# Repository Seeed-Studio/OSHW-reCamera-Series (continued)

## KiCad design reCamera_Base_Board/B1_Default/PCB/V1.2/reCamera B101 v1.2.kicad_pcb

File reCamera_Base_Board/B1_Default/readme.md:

## B1_Default
🎈🎈🎈🎈🎈🎈🎈🎈🎈

**The project contains the 3D housing and circuit design files of the cover board.**

You can use this project to make your own PCB, and the design drawing can also be used as a basic reference for your design.

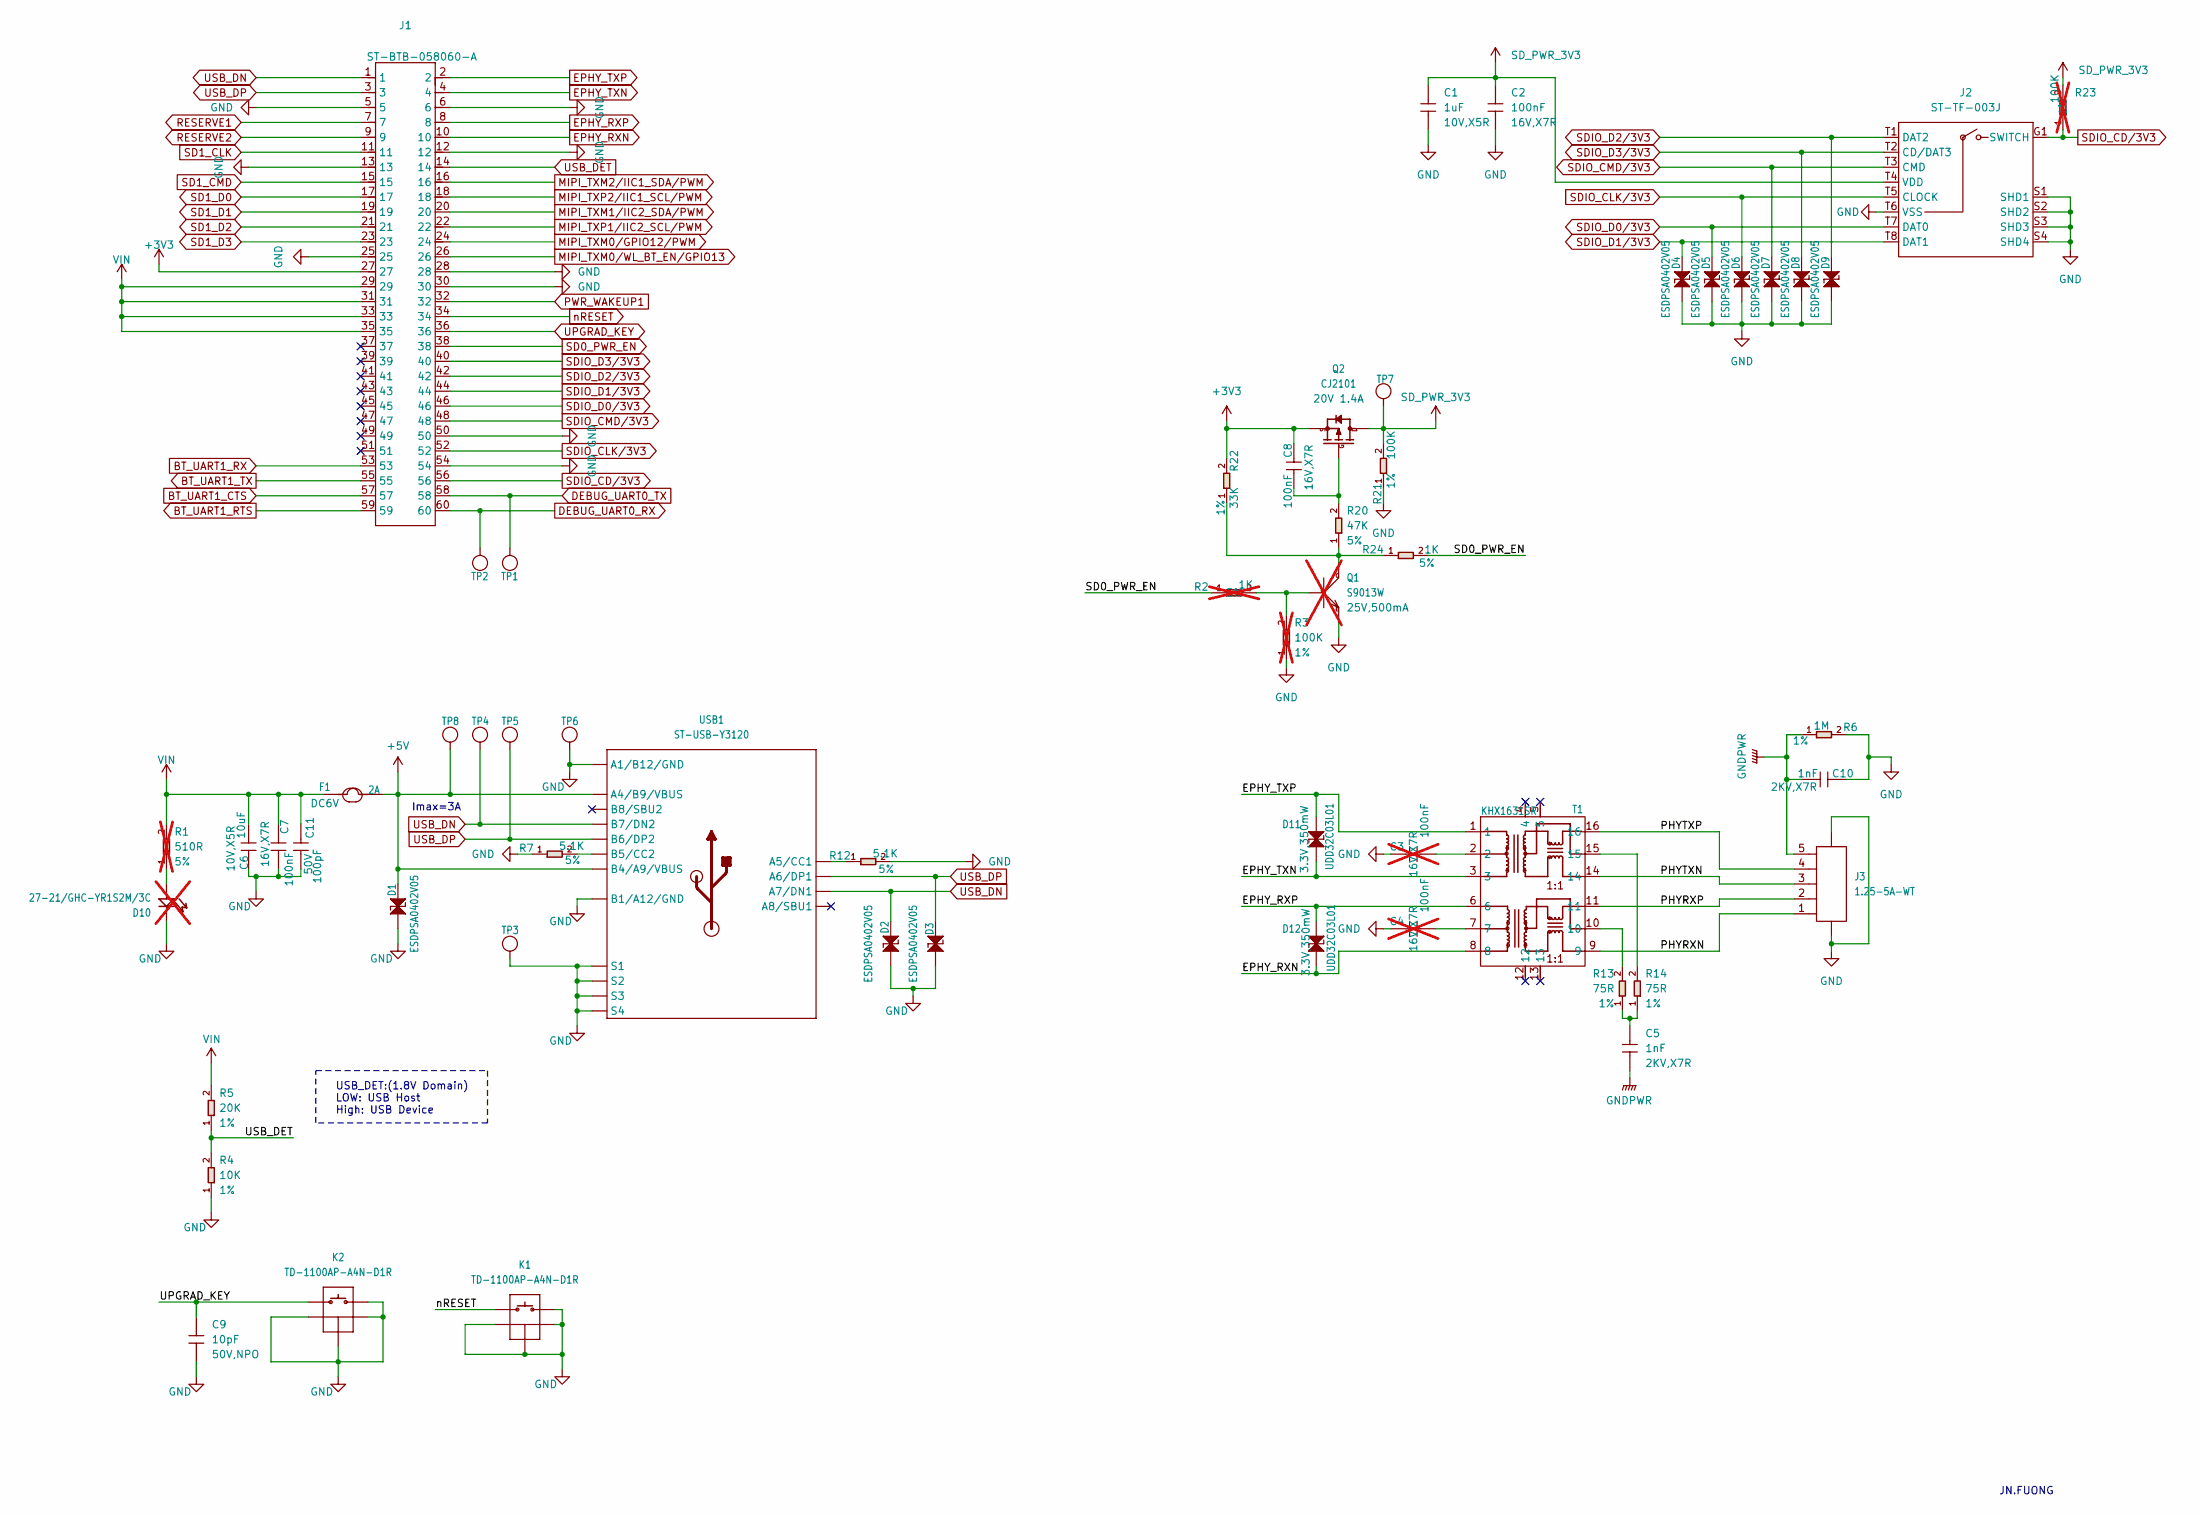
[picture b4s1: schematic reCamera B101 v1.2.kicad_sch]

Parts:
C1: 1uF; C0402; Voltage Rating 10V,X5R; MPN CC0402KRX5R6BB105
C2, C7, C8: 100nF; C0402; Voltage Rating 16V,X7R; MPN CC0402KRX7R7BB104
C3, C4: 100nF; C0402; Voltage Rating 16V,X7R; MPN CC0402KRX7R7BB104; not fitted
C5, C10: 1nF; C1206; Voltage Rating 2KV,X7R; MPN CC1206KKX7RDBB102
C6: 10uF; C0603; Voltage Rating 10V,X5R; MPN CC0603KRX5R6BB106
C9: 10pF; C0402; Voltage Rating 50V,NPO; MPN CC0402JRNPO9BN100
C11: 100pF; C0402; Voltage Rating 50V; MPN CC0402JRNPO9BN101
D1, D2, D3, D4, D5, D6, D7, D8, D9: ESDPSA0402V05; ESD-0402; MPN ESDPSA0402V05
D10: 27-21/GHC-YR1S2M/3C; LED2-0.6X1.7MM; MPN 27-21/GHC-YR1S2M/3C; not fitted
D11, D12: UDD32C03L01; SOD-323; Rating 3.3V,350mW; MPN UDD32C03L01
F1: 2A; F1210; Rating DC6V; MPN SMD1210R200SF
J1: ST-BTB-058060-A; BTB60-Male-Female-0.5-17.7x4.4mm; MPN ST-BTB-058060-A
J2: ST-TF-003J; MICRO-SD-CARD-9P; MPN ST-TF-003J
J3: 1.25-5A-WT; JST5_2P_1d25_7_9x4_3x3_4mm; MPN 1.25-5A-WT
K1, K2: TD-1100AP-A4N-D1R; SW5-SMD-4.56X2.3X1.9MM; MPN TD-1100AP-A4N-D1R
Q1: S9013W; SOT-323; Rating 25V,500mA; MPN S9013W; not fitted
Q2: CJ2101; SOT-323; Rating 20V 1.4A; MPN CJ2101
R1: 510R; R0402; Power Rating 5%; MPN RC0402JR-07510RL; not fitted
R2: 1K; R0402; Power Rating 5%; MPN RC0402JR-071KL; not fitted
R3, R23: 100K; R0402; Power Rating 1%; MPN RC0402FR-07100KL; not fitted
R4: 10K; R0402; Power Rating 1%; MPN RC0402FR-0710KL
R5: 20K; R0402; Power Rating 1%; MPN RC0402FR-0720KL
R6: 1M; R1206; Power Rating 1%; MPN RC1206FR-071ML
R7, R12: 5.1K; R0402; Power Rating 5%; MPN RC0402JR-075K1L
R13, R14: 75R; R0603; Power Rating 1%; MPN RC0603FR-0775RL
R20: 47K; R0402; Power Rating 5%; MPN RC0402JR-0747KL
R21: 100K; R0402; Power Rating 1%; MPN RC0402FR-07100KL
R22: 33K; R0402; Power Rating 1%; MPN RC0402FR-0733KL
R24: 1K; R0402; Power Rating 5%; MPN RC0402JR-071KL
T1: KHX1631SR; TRF_16p_1d27_12d7x7d15x5d1mm; MPN KHX1631SR
TP1, TP2, TP3: Test Point; TP-80X40MIL; Part Type Test Point
TP4, TP5, TP6, TP7, TP8: Test Point; TP-D35MIL; Part Type Test Point
USB1: ST-USB-Y3120; USB2.0-TYPE-C-SMD-12X7.35X3.3MM; MPN ST-USB-Y3120

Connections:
+3V3: C8.1, J1.27, Q2.2 (S), R22.2
+5V: D1.1, F1.2, TP8.1 (T), USB1.A4_B9 (A4/B9/VBUS), USB1.B4_A9 (B4/A9/VBUS)
/PHYRXN: J3.1, T1.9
/PHYRXP: J3.2, T1.11
/PHYTXN: J3.3, T1.14
/PHYTXP: J3.4, T1.16
BT_UART1_CTS: J1.57
BT_UART1_RTS: J1.59
BT_UART1_RX: J1.53
BT_UART1_TX: J1.55
DEBUG_UART0_RX: J1.60, TP2.1 (T)
DEBUG_UART0_TX: J1.58, TP1.1 (T)
EPHY_RXN: D12.1, J1.10, T1.8
EPHY_RXP: D12.2, J1.8, T1.6
EPHY_TXN: D11.1, J1.4, T1.3
EPHY_TXP: D11.2, J1.2, T1.1
GND: C1.2, C2.2, C3.1, C4.1, C6.2, C7.2, C9.2, C10.1, C11.2, D1.2, D2.2, D3.2, D4.2, D5.2, D6.2, D7.2, D8.2, D9.2, D10.2 (-), J1.5, J1.6, J1.12, J1.13, J1.25, J1.28, J1.30, J1.50, J1.54, J2.S1 (SHD1), J2.S2 (SHD2), J2.S3 (SHD3), J2.S4 (SHD4), J2.T6 (VSS), J3.6, J3.7, K1.2, K1.S1, K1.S2, K1.S3, K2.2, K2.S1, K2.S2, K2.S3, Q1.2 (E), R3.1, R4.1, R6.2, R7.1, R12.2, R21.1, TP3.1 (T), TP6.1 (T), USB1.A1_B12 (A1/B12/GND), USB1.B1_A12 (B1/A12/GND), USB1.S1, USB1.S2, USB1.S3, USB1.S4
GNDPWR: C5.2, C10.2, J3.5, R6.1
MIPI_TXM0/GPIO12/PWM: J1.24
MIPI_TXM0/WL_BT_EN/GPIO13: J1.26
MIPI_TXM1/IIC2_SDA/PWM: J1.20
MIPI_TXM2/IIC1_SDA/PWM: J1.16
MIPI_TXP1/IIC2_SCL/PWM: J1.22
MIPI_TXP2/IIC1_SCL/PWM: J1.18
unnamed: C3.2, T1.2
unnamed: C4.2, T1.7
unnamed: C5.1, R13.1, R14.1
unnamed: D10.1 (+), R1.1
unnamed: Q1.1 (B), R2.2, R3.2
unnamed: Q1.3 (C), R20.1, R22.1, R24.1
unnamed: C8.2, Q2.1 (G), R20.2
unnamed: R13.2, T1.10
unnamed: R14.2, T1.15
unnamed: R12.1, USB1.A5 (A5/CC1)
unnamed: R7.2, USB1.B5 (B5/CC2)
PWR_WAKEUP1: J1.32
RESERVE1: J1.7
RESERVE2: J1.9
SD0_PWR_EN: J1.38, R2.1, R24.2
SD1_CLK: J1.11
SD1_CMD: J1.15
SD1_D0: J1.17
SD1_D1: J1.19
SD1_D2: J1.21
SD1_D3: J1.23
SDIO_CD/3V3: J1.56, J2.G1 (SWITCH), R23.1
SDIO_CLK/3V3: D6.1, J1.52, J2.T5 (CLOCK)
SDIO_CMD/3V3: D7.1, J1.48, J2.T3 (CMD)
SDIO_D0/3V3: D5.1, J1.46, J2.T7 (DAT0)
SDIO_D1/3V3: D4.1, J1.44, J2.T8 (DAT1)
SDIO_D2/3V3: D9.1, J1.42, J2.T1 (DAT2)
SDIO_D3/3V3: D8.1, J1.40, J2.T2 (CD/DAT3)
SD_PWR_3V3: C1.1, C2.1, J2.T4 (VDD), Q2.3 (D), R21.2, R23.2, TP7.1 (T)
UPGRAD_KEY: C9.1, J1.36, K2.1
USB_DET: J1.14, R4.2, R5.1
USB_DN: D2.1, J1.1, TP4.1 (T), USB1.A7 (A7/DN1), USB1.B7 (B7/DN2)
USB_DP: D3.1, J1.3, TP5.1 (T), USB1.A6 (A6/DP1), USB1.B6 (B6/DP2)
VIN: C6.1, C7.1, C11.1, F1.1, J1.29, J1.31, J1.33, J1.35, R1.2, R5.2
nRESET: J1.34, K1.1

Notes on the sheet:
JN.FUONG
USB_DET:(1.8V Domain) LOW: USB Host High: USB Device
Imax=3A

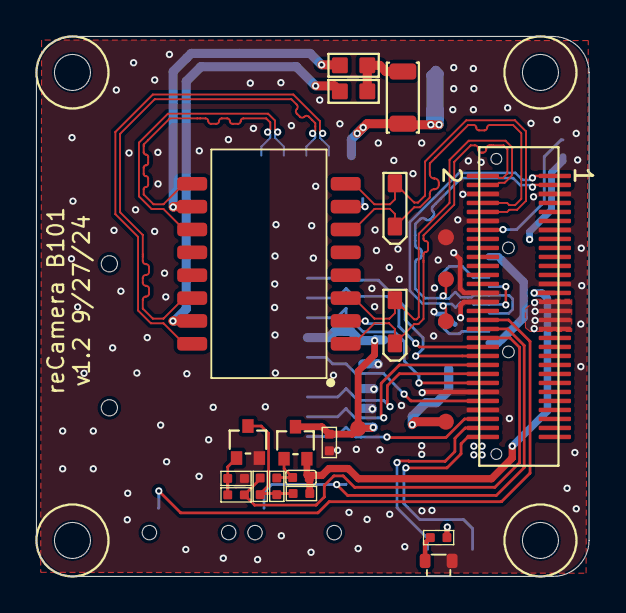
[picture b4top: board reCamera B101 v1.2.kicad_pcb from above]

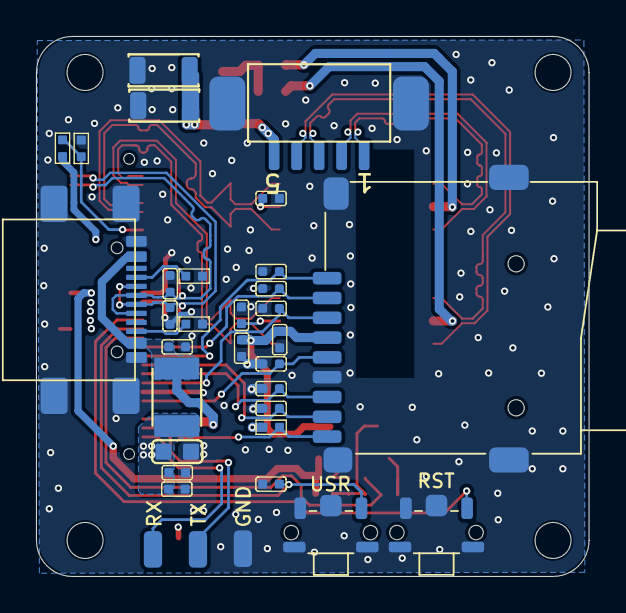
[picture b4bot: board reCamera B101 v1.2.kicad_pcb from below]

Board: 4 copper layers, 30.7 x 30.0 mm, 56 parts (33 on the bottom side), 40 nets.

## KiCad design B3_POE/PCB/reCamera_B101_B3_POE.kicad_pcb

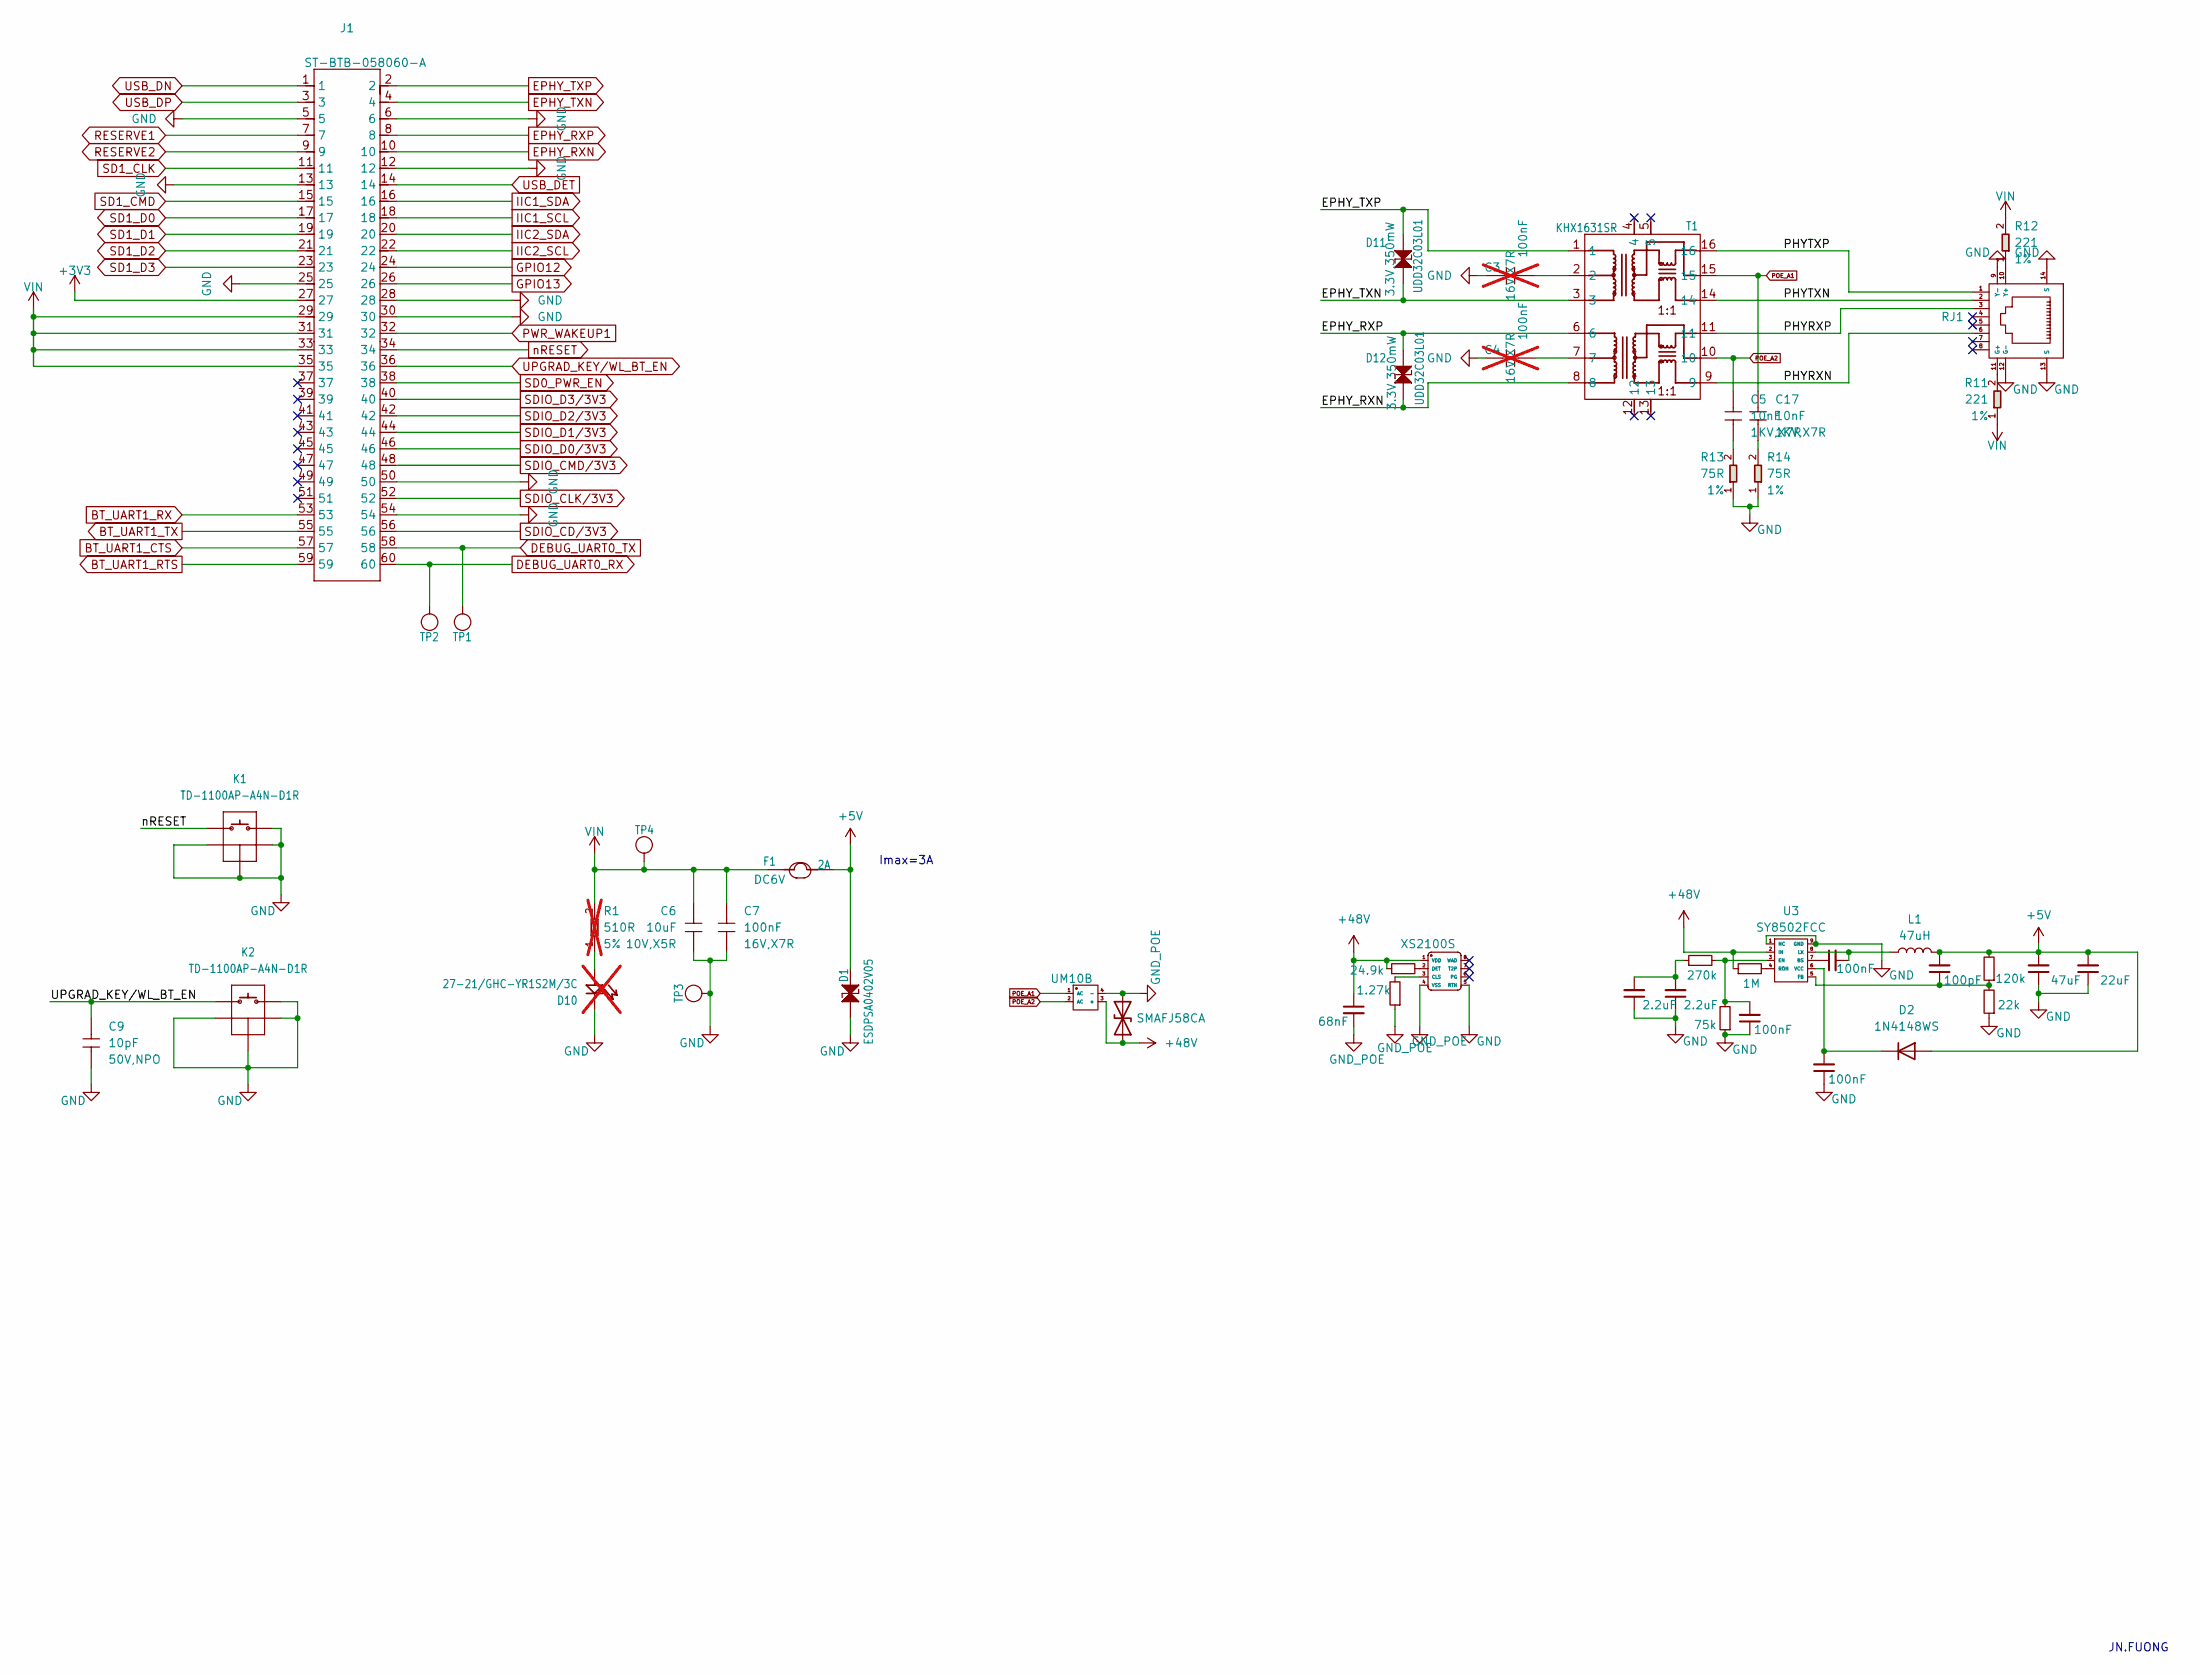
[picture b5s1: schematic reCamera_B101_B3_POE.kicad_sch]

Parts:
C1: 68nF; C_0402_1005Metric
C2, C10: 2.2uF; C_0402_1005Metric
C3, C4: 100nF; C0402; Voltage Rating 16V,X7R; MPN CC0402KRX7R7BB104; not fitted
C5, C17: 10nF; C0402; Voltage Rating 1KV,X7R; MPN CC1206KKX7RCBB102
C6: 10uF; C0402; Voltage Rating 10V,X5R; MPN CC0603KRX5R6BB106
C7: 100nF; C0402; Voltage Rating 16V,X7R; MPN CC0402KRX7R7BB104
C9: 10pF; C0402; Voltage Rating 50V,NPO; MPN CC0402JRNPO9BN100
C11, C12, C13: 100nF; C_0402_1005Metric
C14: 100pF; C_0402_1005Metric
C15: 47uF; C_0402_1005Metric
C16: 22uF; C_0402_1005Metric
D1: ESDPSA0402V05; ESD-0402; MPN ESDPSA0402V05
D2: 1N4148WS; D_SOD-323
D10: 27-21/GHC-YR1S2M/3C; LED2-0.6X1.7MM; MPN 27-21/GHC-YR1S2M/3C; not fitted
D11, D12: UDD32C03L01; SOD-323; Rating 3.3V,350mW; MPN UDD32C03L01
D13: SMAFJ58CA; SMAF_L3.5-W2.6-LS4.7-BI
F1: 2A; F1210; Rating DC6V; MPN SMD1210R200SF
J1: ST-BTB-058060-A; BTB60-Male-Female-0.5-17.7x4.4mm; MPN ST-BTB-058060-A
K1, K2: TD-1100AP-A4N-D1R; SW5-SMD-4.56X2.3X1.9MM; MPN TD-1100AP-A4N-D1R
L1: 47uH; L_7.3x7.3_H3.5
R1: 510R; R0402; Power Rating 5%; MPN RC0402JR-07510RL; not fitted
R4: 1.27k; R_0402_1005Metric
R5: 24.9k; R_0402_1005Metric
R6: 270k; R_0402_1005Metric
R7: 75k; R_0402_1005Metric
R8: 1M; R_0402_1005Metric
R9: 120k; R_0402_1005Metric
R10: 22k; R_0402_1005Metric
R11, R12: 221; C0402; Power Rating 1%; MPN RC0603FR-0775RL
R13, R14: 75R; C0402; Power Rating 1%; MPN RC0603FR-0775RL
RJ1: R-RJ45S08P-C000
T1: KHX1631SR; TRF_16p_1d27_12d7x7d15x5d1mm; MPN KHX1631SR
TP1, TP2, TP3, TP4: Test Point; TP; Part Type Test Point
U1: UM10B; UMB-4_L3.8-W3.6-P2.50-LS4.9-BL
U2: XS2100S; SOP-8_L4.9-W3.9-P1.27-LS6.0-BL
U3: SY8502FCC; SOIC-8_L4.9-W3.9-P1.27-LS6.0-BL-EP

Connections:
+3V3: J1.27
+5V: C14.2, C15.2, C16.2, D1.1, D2.2 (A), F1.2, L1.2, R9.2
+48V: C1.1, D13.1 (A1), R5.1, R8.1, U1.3 (+), U2.1 (VDD), U3.2 (IN)
/PHYRXN: RJ1.6, T1.9
/PHYRXP: RJ1.3, T1.11
/PHYTXN: RJ1.2, T1.14
/PHYTXP: RJ1.1, T1.16
BT_UART1_CTS: J1.57
BT_UART1_RTS: J1.59
BT_UART1_RX: J1.53
BT_UART1_TX: J1.55
DEBUG_UART0_RX: J1.60, TP2.1 (T)
DEBUG_UART0_TX: J1.58, TP1.1 (T)
EPHY_RXN: D12.1, J1.10, T1.8
EPHY_RXP: D12.2, J1.8, T1.6
EPHY_TXN: D11.1, J1.4, T1.3
EPHY_TXP: D11.2, J1.2, T1.1
GND: C2.1, C3.1, C4.1, C6.2, C7.2, C9.2, C10.1, C11.1, C12.1, C15.1, C16.1, D1.2, D10.2 (-), J1.5, J1.6, J1.12, J1.13, J1.25, J1.28, J1.30, J1.50, J1.54, K1.2, K1.S1, K1.S2, K1.S3, K2.2, K2.S1, K2.S2, K2.S3, R7.1, R10.1, R13.1, R14.1, RJ1.9 (Y-), RJ1.12 (G-), RJ1.13 (S), RJ1.14 (S), TP3.1 (T), U2.5 (RTN), U3.1 (NC), U3.9 (GND)
GND_POE: C1.2, D13.2 (A2), R4.1, U1.4 (-), U2.4 (VSS)
GPIO12: J1.24
GPIO13: J1.26
IIC1_SCL: J1.18
IIC1_SDA: J1.16
IIC2_SCL: J1.22
IIC2_SDA: J1.20
unnamed: C3.2, T1.2
unnamed: C4.2, T1.7
unnamed: C5.2, R13.2
unnamed: C2.2, C10.2, R6.1
unnamed: C17.2, R14.2
unnamed: C12.2, D2.1 (K), U3.6 (VCC)
unnamed: D10.1 (+), R1.1
unnamed: R11.2, RJ1.11 (G+)
unnamed: R12.1, RJ1.10 (Y+)
unnamed: R4.2, U2.3 (CLS)
unnamed: R5.2, U2.2 (DET)
unnamed: C13.1, U3.7 (BS)
unnamed: C11.2, R6.2, R7.2, U3.3 (EN)
unnamed: C14.1, R9.1, R10.2, U3.5 (FB)
unnamed: C13.2, L1.1, U3.8 (LX)
unnamed: R8.2, U3.4 (RON)
POE_A1: C17.1, T1.15, U1.1 (AC)
POE_A2: C5.1, T1.10, U1.2 (AC)
PWR_WAKEUP1: J1.32
RESERVE1: J1.7
RESERVE2: J1.9
SD0_PWR_EN: J1.38
SD1_CLK: J1.11
SD1_CMD: J1.15
SD1_D0: J1.17
SD1_D1: J1.19
SD1_D2: J1.21
SD1_D3: J1.23
SDIO_CD/3V3: J1.56
SDIO_CLK/3V3: J1.52
SDIO_CMD/3V3: J1.48
SDIO_D0/3V3: J1.46
SDIO_D1/3V3: J1.44
SDIO_D2/3V3: J1.42
SDIO_D3/3V3: J1.40
UPGRAD_KEY/WL_BT_EN: C9.1, J1.36, K2.1
USB_DET: J1.14
USB_DN: J1.1
USB_DP: J1.3
VIN: C6.1, C7.1, F1.1, J1.29, J1.31, J1.33, J1.35, R1.2, R11.1, R12.2, TP4.1 (T)
nRESET: J1.34, K1.1

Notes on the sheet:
JN.FUONG
Imax=3A

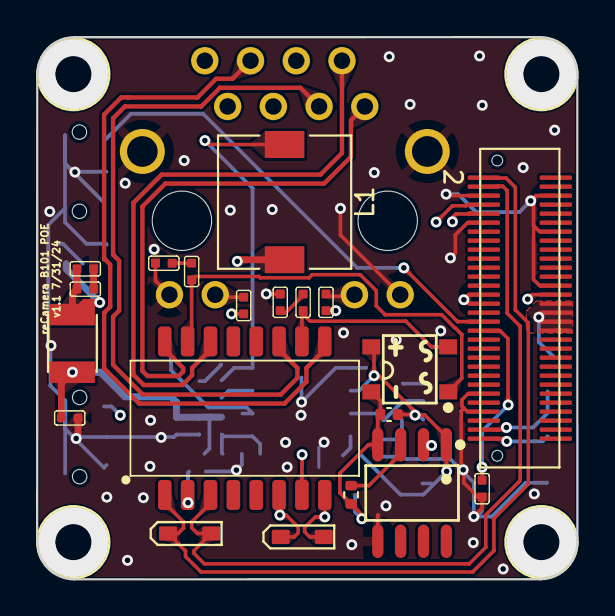
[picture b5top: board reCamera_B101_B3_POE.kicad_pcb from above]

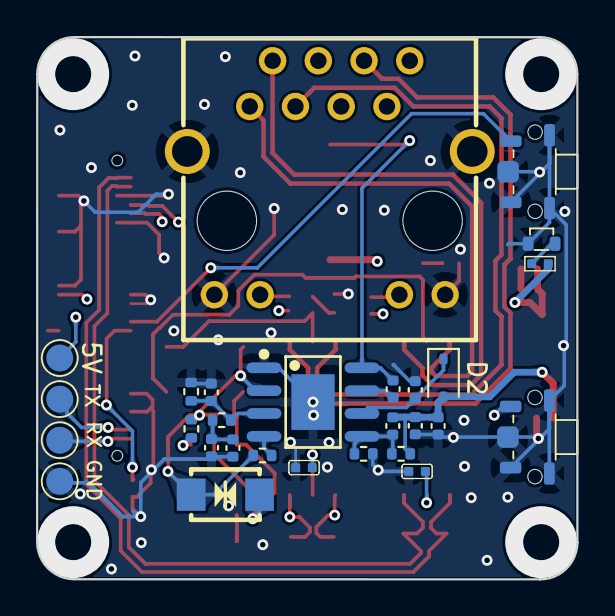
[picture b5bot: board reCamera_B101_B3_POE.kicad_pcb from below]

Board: 4 copper layers, 30.0 x 30.1 mm, 48 parts (28 on the bottom side), 35 nets.

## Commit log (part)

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2024-08-01 docs: project structure init
2024-08-06 [doc] add standard boards readme
2024-08-06 [fix] use raw html for image
2024-08-06 [fix] restore readme.md
2024-08-07 [fix] revise the readme.md
2024-08-07 [fix] Add reCamera-Gimbal-1.png
2024-08-07 [fix] S1_OV5647/s101-readme.md: fix typo
2024-08-07 [fix] change the camera name to OV5647
2024-08-07 [fix] Update S1_OV5647/s101-readme.md
2024-08-07 [fix] add Model for OV5647 camera
2024-08-09 [fix]: reCamera is not ReCamera
2024-08-13 [fix]
2024-08-15 [doc] update software projects
2024-08-15 Rename 20b716f188346082ae41970eb1b7215.png to B1_Default_Bottom.png
2024-08-15 Rename 233ed49bf09d4f877fda6c783545a1c.png to B1_Default_Upper.png
2024-08-15 Rename a1820e9c1d215a653db6a6fbe115e7e.png to B1_Default_sch.png
2024-08-15 Rename efaac50a4a5e071a0dab4a029c1c640.png to B1_POE_sch.png
2024-08-15 Rename B1_Default/recamera_B1_.stp to B1_Default/Model/recamera_B1_Default.stp
2024-08-15 Rename B1_Default/reCamera B101 v0.1.kicad_pro to B1_Default/PCB/reCamera B101 v0.1.kicad_pro
2024-08-15 Rename B2_POE/reCamera_B101_RJ45.kicad_pro to B2_POE/PCB/reCamera_B101_RJ45.kicad_pro
2024-08-15 chore: Update core board features and version info
2024-08-15 File structure changed
2024-08-15 Fix image paths in readme.md
2024-08-15 picture change
2024-08-15 Update core board features and version info
2024-08-15 Upload the New Board
2024-08-16 PIC changed
2024-08-16 Changed B3 and B4
2024-08-16 [fix] add readme.md and statics
2024-08-16 [fix]add images
2024-08-16 Add S2_IMX335 and S3_SC130GS readme files
2024-08-19 chore: Update reCamera Web frontend link
2024-08-19 POE Changed
2024-08-20 chore: Fix typo in readme.md
2024-08-20 Create LICENSE
2024-08-21 chore: Update reCamera Gimbal image in readme.md
2024-08-22 [fix]add Sensor list
2024-08-23 Rename 企业微信截图_17243809714874.png to B3_POE_sch.png
2024-08-23 Rename reCamera_B101_RJ45.kicad_pro to reCamera_B101_POE.kicad_pro
2024-08-24 Add discord link
2024-08-24 chore: Add Discord group invitation link to readme.md
2024-09-09 PoE Modified
2024-09-11 B101 V1.0 & V1.1
2024-09-11 reCamera_Pocket
2024-09-11 reCamera_pocket update
2024-09-11 pocket
2024-09-18 Rename 427b60a50cdec68b545c81bb3820fad.png to B3_POE_sch.png
2024-10-08 Add sync_issues GitHub Action for workflows
2024-10-23 [fix]add C1 PCB files
2024-11-01 Update C1, B1, S1
2024-11-01 Change C1 Board file path
2024-11-01 update files
2024-11-01 Update readme.md with social media sharing buttons and badges
2024-11-14 [fix]changed readme
2024-11-29 update B1 S1 C1 board image
2024-12-03 [fix]changed images
2024-12-10 [fix]add Gimbal files
2024-12-10 [fix]changed reCamera_Gimbal
2024-12-10 [fix]change readme.md
2024-12-11 [fix]change recamera Gimbal files
2024-12-13 [fix]add video
2024-12-13 [fix]add Dashboard project
2024-12-13 更新 recamera Gimbal 文件
2025-01-08 ci: add an action to automatically close stale issues and PRs
2025-01-23 Add the roadmap.md document. Completed the Gimbal development related materials
2025-02-06 restructure the repository
2025-02-06 add pictures and video
2025-02-07 update README file and image
2025-02-07 update README images link
2025-02-08 upload public dashboard to example
2025-02-11 add readme software structure
2025-02-11 Change B4's image configuration
2025-02-11 Changing the image path
2025-02-12 Add 3D printed files for B2 and B3
2025-02-12 change flow examples and read me
2025-02-12 change readme
2025-02-12 Change the gimabl init code
2025-02-18 add gimbal dashboard 1.0
2025-02-21 Modify the motor protocol documentation.
2025-02-27 [fix] add gimbal dashboard flow
2025-03-12 fix: fix an issue where the recamera_B1_Default.stp file was empty
2025-03-17 [fix] add Gimbal gcc host-tools
2025-03-17 [fix] Modify the Gimbal readme
2025-03-20 Update OV5647 specification
2025-03-20 Update software development guide.
2025-04-01 Add CAN protocol specification in English
2025-04-08 files modification
2025-04-09 Modify some 3D printed files
2025-04-11 [fix] Modification readme
2025-04-11 [fix] Motification Gimbal src
2025-04-11 Modification of the Makefile
2025-04-30 add core cooler 3D printed files
2025-05-15 add Gimbal Power supply board files
2025-06-30 Add recognition models for drones and birds
2025-06-30 [fix] Changing file location
2025-07-04 add(Real_time_YOLO_object_detection):add new demo of reCamera
2025-07-09 add(Cpp_project): add the cpp project folder
2025-07-14 add(Supervisor_add_detection_http):add new c++ project of reCamera
2025-07-17 [fix] Add reCamera POE and GC2053 Sensor Information
2025-07-17 [fix] Add reCamera POE and GC2053 Sensor Information
2025-07-27 Updated Preview Page block, added support for automatic resize preview based on selected model resolution and fps
2025-07-28 Fix links
2025-09-21 [fix] Added the PCB documents for Poe and GC2053. Added some YOLO11 models.
2025-10-09 [fix] Fix some errors
2025-10-23 [add] add reCamera_Microscope Project
2025-10-28 [fix] fix readme.md
2025-10-28 [fix] add IO pics
2025-12-03 更新了三张PCB
2026-01-13 更新了一张reCamera POE的PCB和原理图
